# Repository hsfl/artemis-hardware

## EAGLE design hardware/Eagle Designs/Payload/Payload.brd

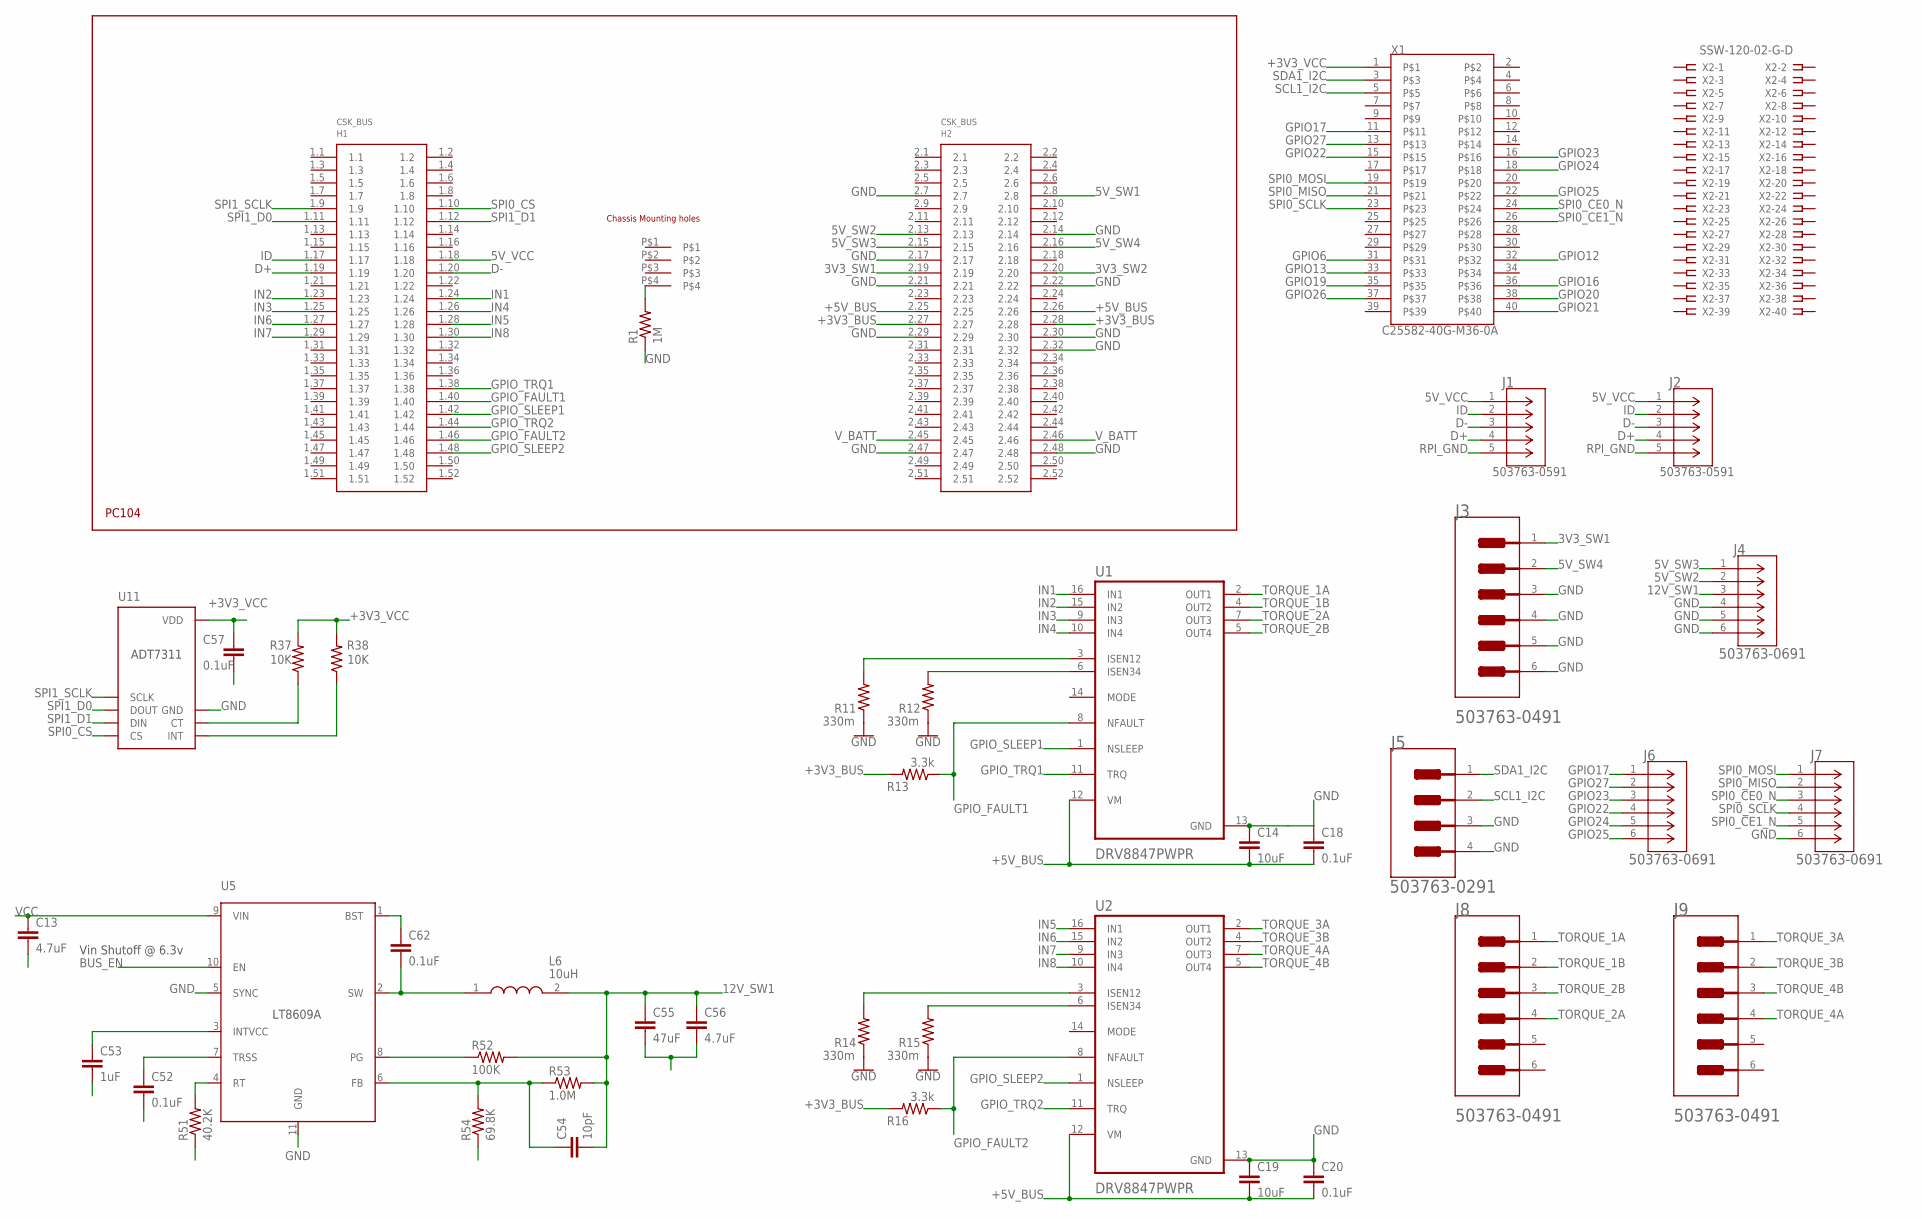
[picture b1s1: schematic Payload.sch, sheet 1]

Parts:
C13, C56: 4.7uF; 0805
C14, C19: 10uF; 0805
C18, C20, C52, C57, C62: 0.1uF; 0805
C53: 1uF; 0805
C54: 10pF; 0805
C55: 47uF; 1210
H1: PC104_WCONN
J1, J2: 503763-0591; CONN_5037630591_MOL
J3, J8, J9: MOLEX_503763-0491MOLEX_503763-0491_0_0; MOLEX_503763-0491_0
J4, J6, J7: 503763-0691; CONN_503763-0691_MOL
J5: MOLEX_503763-0291MOLEX_503763-0291_0_0; MOLEX_503763-0291_0
L6: 10uH; XFL4030472MEB
R1: 1M; 0805
R11, R12, R14, R15: 330m; 0805
R13, R16: 3.3k; 0805
R37, R38: 10K; 0805
R51: 40.2K; 0805
R52: 100K; 0805
R53: 1.0M; 0805
R54: 69.8K; 0805
U1, U2: DRV8847PWPR; SOP65P640X120-17N
U5: LT8609A; MSOP-10_MSE
U11: ADT7311; SOIC-8
X1: C25582-40G-M36-0A; ADAFRUIT_C25582-40G-M36-0A_0
X2: SSW-120-02-G-D

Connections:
3V3_SW1: H1.2.19, J3.1
3V3_SW2: H1.2.20
5V_SW1: H1.2.8
5V_SW2: H1.2.13, J4.2
5V_SW3: H1.2.15, J4.1
5V_SW4: H1.2.16, J3.2
5V_VCC: H1.1.18, J1.1, J2.1
12V_SW1: C54.2, C55.1, C56.1, J4.3, L6.2, R52.2, R53.2
+3V3_BUS: H1.2.27, H1.2.28, R13.2, R16.2
+3V3_VCC: C57.1, R37.2, R38.2, U11.8 (VDD), X1.1
+5V_BUS: C14.2, C18.2, C19.2, C20.2, H1.2.25, H1.2.26, U1.12 (VM), U2.12 (VM)
BST_3V3_BUS: C62.1, U5.1 (BST)
BUS_EN: U5.10 (EN)
D+: H1.1.19, J1.4, J2.4
D-: H1.1.20, J1.3, J2.3
FB_3V3_BUS: C54.1, R53.1, R54.2, U5.6 (FB)
GND: C14.1, C18.1, C19.1, C20.1, C52.2, C53.2, C55.2, C56.2, C57.2, H1.2.7, H1.2.14, H1.2.17, H1.2.21, H1.2.22, H1.2.29, H1.2.30, H1.2.32, H1.2.47, H1.2.48, J3.3, J3.4, J3.5 (MNT_1), J3.6 (MNT_2), J4.4, J4.5, J4.6, J5.3 (MNT_1), J5.4 (MNT_2), J7.6, R1.1, R11.1, R12.1, R14.1, R15.1, R51.1, R54.1, U1.13 (GND), U2.13 (GND), U5.5 (SYNC), U5.11 (GND), U11.7 (GND); also elsewhere on the board
GND1: C13.2
GPIO6: X1.31
GPIO12: X1.32
GPIO13: X1.33
GPIO16: X1.36
GPIO17: J6.1, X1.11
GPIO19: X1.35
GPIO20: X1.38
GPIO21: X1.40
GPIO22: J6.4, X1.15
GPIO23: J6.3, X1.16
GPIO24: J6.5, X1.18
GPIO25: J6.6, X1.22
GPIO26: X1.37
GPIO27: J6.2, X1.13
GPIO_FAULT1: H1.1.40, R13.1, U1.8 (NFAULT)
GPIO_FAULT2: H1.1.46, R16.1, U2.8 (NFAULT)
GPIO_SLEEP1: H1.1.42, U1.1 (NSLEEP)
GPIO_SLEEP2: H1.1.48, U2.1 (NSLEEP)
GPIO_TRQ1: H1.1.38, U1.11 (TRQ)
GPIO_TRQ2: H1.1.44, U2.11 (TRQ)
ID: H1.1.17, J1.2, J2.2
IN1: H1.1.24, U1.16 (IN1)
IN2: H1.1.23, U1.15 (IN2)
IN3: H1.1.25, U1.9 (IN3)
IN4: H1.1.26, U1.10 (IN4)
IN5: H1.1.28, U2.16 (IN1)
IN6: H1.1.27, U2.15 (IN2)
IN7: H1.1.29, U2.9 (IN3)
IN8: H1.1.30, U2.10 (IN4)
unnamed: H1.P$4, R1.2
unnamed: R12.2, U1.6 (ISEN34)
unnamed: R11.2, U1.3 (ISEN12)
unnamed: R15.2, U2.6 (ISEN34)
unnamed: R14.2, U2.3 (ISEN12)
PG_3V3_BUS: R52.1, U5.8 (PG)
RPI_GND: J1.5, J2.5
RT_3V3_BUS: R51.2, U5.4 (RT)
SCL1_I2C: J5.2, X1.5
SDA1_I2C: J5.1, X1.3
SPI0_CE0_N: J7.3, X1.24
SPI0_CE1_N: J7.5, X1.26
SPI0_CS: H1.1.10, U11.4 (CS)
SPI0_MISO: J7.2, X1.21
SPI0_MOSI: J7.1, X1.19
SPI0_SCLK: J7.4, X1.23
SPI1_D0: H1.1.11, U11.2 (DOUT)
SPI1_D1: H1.1.12, U11.3 (DIN)
SPI1_SCLK: H1.1.9, U11.1 (SCLK)
SW_3V3_BUS: C62.2, L6.1, U5.2 (SW)
TORQUE_1A: J8.1, U1.2 (OUT1)
TORQUE_1B: J8.2, U1.4 (OUT2)
TORQUE_2A: J8.4, U1.7 (OUT3)
TORQUE_2B: J8.3, U1.5 (OUT4)
TORQUE_3A: J9.1, U2.2 (OUT1)
TORQUE_3B: J9.2, U2.4 (OUT2)
TORQUE_4A: J9.4, U2.7 (OUT3)
TORQUE_4B: J9.3, U2.5 (OUT4)
TRSS_3V3_BUS: C52.1, U5.7 (TRSS)
U11_CT: R37.1, U11.6 (CT)
U11_INT: R38.1, U11.5 (INT)
VCC: C13.1, U5.9 (VIN); also elsewhere on the board
VCC_3V3_BUS: C53.1, U5.3 (INTVCC)
V_BATT: H1.2.45, H1.2.46; also elsewhere on the board

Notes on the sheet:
Vin Shutoff @ 6.3v

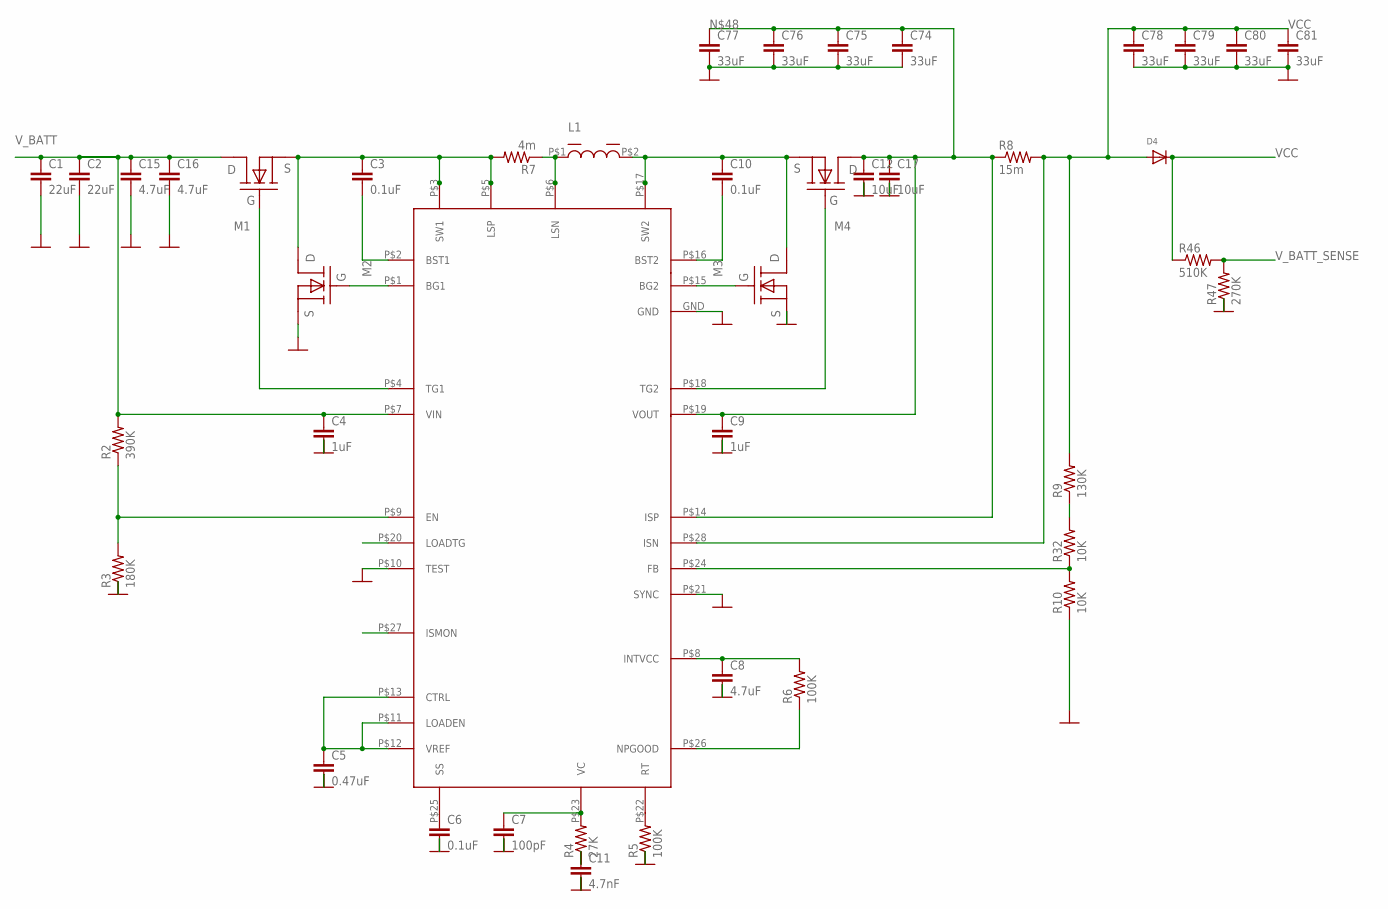
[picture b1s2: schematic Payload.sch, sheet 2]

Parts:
C1, C2: 22uF; 0805
C3, C6, C10: 0.1uF; 0805
C4, C9: 1uF; 0805
C5: 0.47uF; 0805
C7: 100pF; 0805
C8, C15, C16: 4.7uF; 0805
C11: 4.7nF; 0805
C12, C17: 10uF; 0805
C74, C75, C76, C77, C78, C79, C80, C81: 33uF; 1206
D4: DIODE_SOD-123FL; SOD-123FL
L1: 6uH; 7443551600
M1, M2: BSZ100N06LS3
M3, M4: BSZ033NE2LS5; BSZ100N06LS3
R2: 390K; 0805
R3: 180K; 0805
R4: 27K; 0805
R5, R6: 100K; 0805
R7: 4m; 0805
R8: 15m; 0805
R9: 130K; 0805
R10, R32: 10K; 0805
R46: 510K; 0805
R47: 270K; 0805
U$2: LT8309EFE

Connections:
GND: C1.2, C2.2, C4.2, C5.2, C6.2, C7.2, C8.2, C9.2, C11.2, C12.2, C15.2, C16.2, C17.2, C74.2, C75.2, C76.2, C77.2, C78.2, C79.2, C80.2, C81.2, M2.P$2 (S), M2.P$3 (S), M2.P$4 (S), M3.P$2 (S), M3.P$3 (S), M3.P$4 (S), R3.1, R5.1, R10.1, R47.1, U$2.GND, U$2.P$10 (TEST), U$2.P$21 (SYNC); also elsewhere on the board
unnamed: C3.1, M1.P$2 (S), M1.P$3 (S), M1.P$4 (S), M2.P$5 (D), M2.P$6 (D), M2.P$7 (D), M2.P$8 (D), M2.P$9 (D), R7.2, U$2.P$3 (SW1), U$2.P$5 (LSP)
unnamed: C3.2, U$2.P$2 (BST1)
unnamed: C6.1, U$2.P$25 (SS)
unnamed: R5.2, U$2.P$22 (RT)
unnamed: C10.1, L1.P$2, M3.P$5 (D), M3.P$6 (D), M3.P$7 (D), M3.P$8 (D), M3.P$9 (D), M4.P$2 (S), M4.P$3 (S), M4.P$4 (S), U$2.P$17 (SW2)
unnamed: R9.1, R32.2
unnamed: M2.P$1 (G), U$2.P$1 (BG1)
unnamed: M1.P$1 (G), U$2.P$4 (TG1)
unnamed: M3.P$1 (G), U$2.P$15 (BG2)
unnamed: R2.1, R3.2, U$2.P$9 (EN)
unnamed: C5.1, U$2.P$11 (LOADEN), U$2.P$12 (VREF), U$2.P$13 (CTRL)
unnamed: C7.1, R4.2, U$2.P$23 (VC)
unnamed: R6.1, U$2.P$26 (NPGOOD)
unnamed: C8.1, R6.2, U$2.P$8 (INTVCC)
unnamed: L1.P$1, R7.1, U$2.P$6 (LSN)
unnamed: C10.2, U$2.P$16 (BST2)
unnamed: C9.1, C12.1, C17.1, C74.1, C75.1, C76.1, C77.1, M4.P$5 (D), M4.P$6 (D), M4.P$7 (D), M4.P$8 (D), M4.P$9 (D), R8.1, U$2.P$14 (ISP), U$2.P$19 (VOUT)
unnamed: M4.P$1 (G), U$2.P$18 (TG2)
unnamed: R10.2, R32.1, U$2.P$24 (FB)
unnamed: C11.1, R4.1
VCC: C78.1, C79.1, C80.1, C81.1, D4.A, D4.C, R8.2, R9.2, R46.1, U$2.P$28 (ISN); also elsewhere on the board
V_BATT: C1.1, C2.1, C4.1, C15.1, C16.1, M1.P$5 (D), M1.P$6 (D), M1.P$7 (D), M1.P$8 (D), M1.P$9 (D), R2.2, U$2.P$7 (VIN); also elsewhere on the board
V_BATT_SENSE: R46.2, R47.2

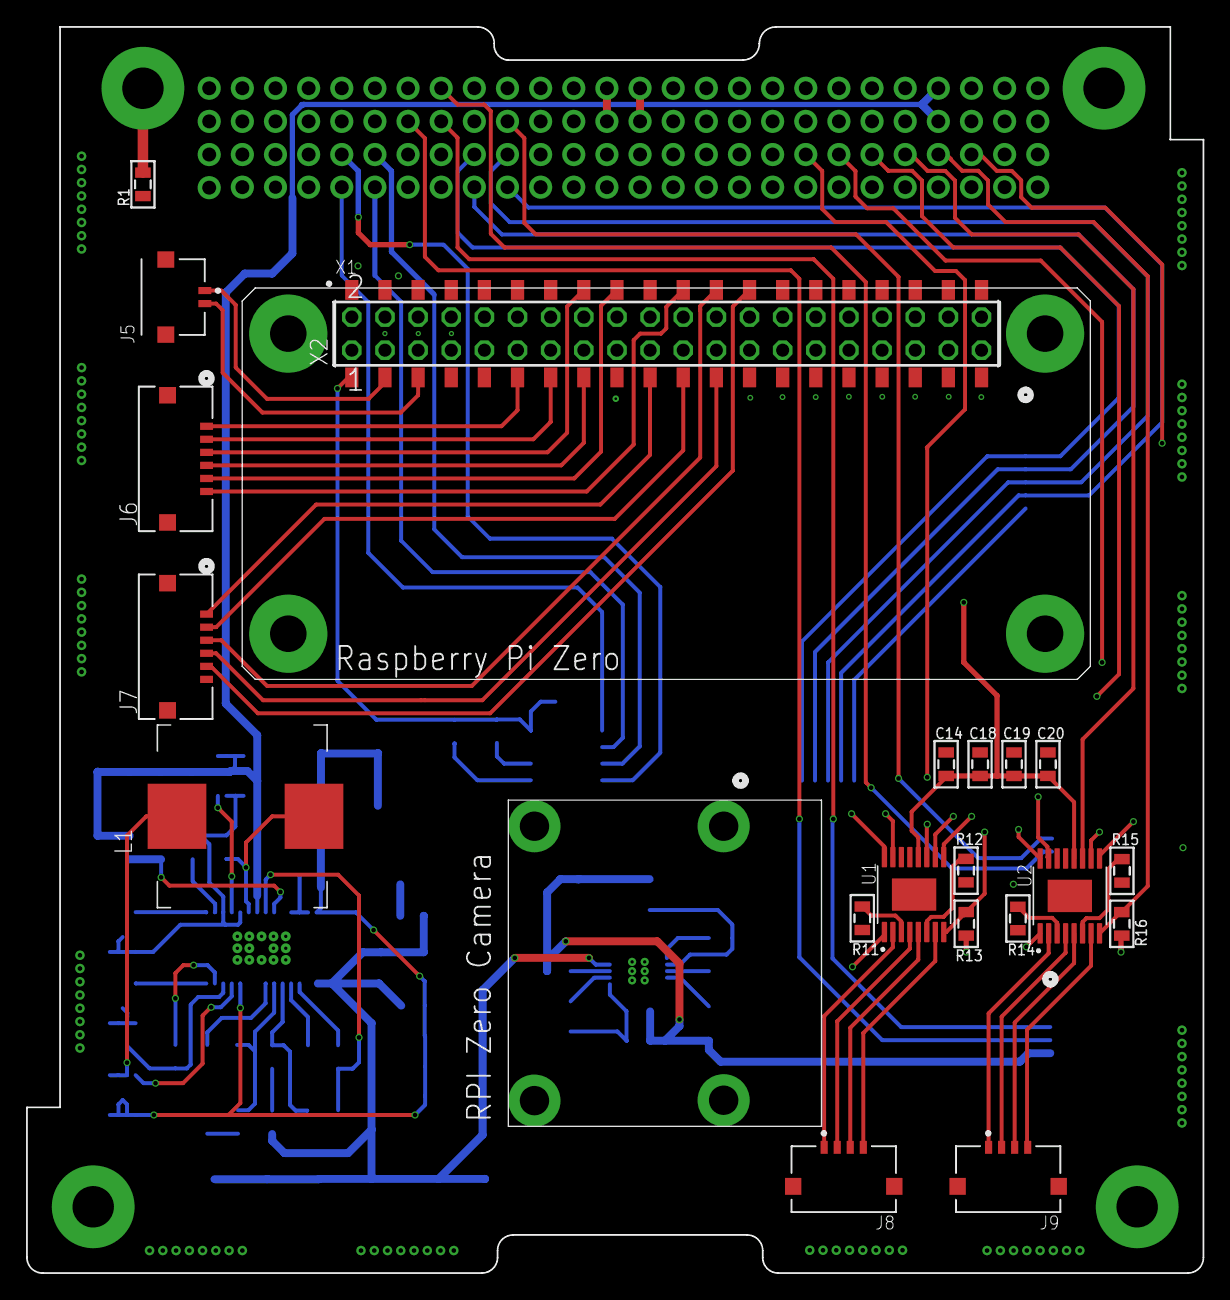
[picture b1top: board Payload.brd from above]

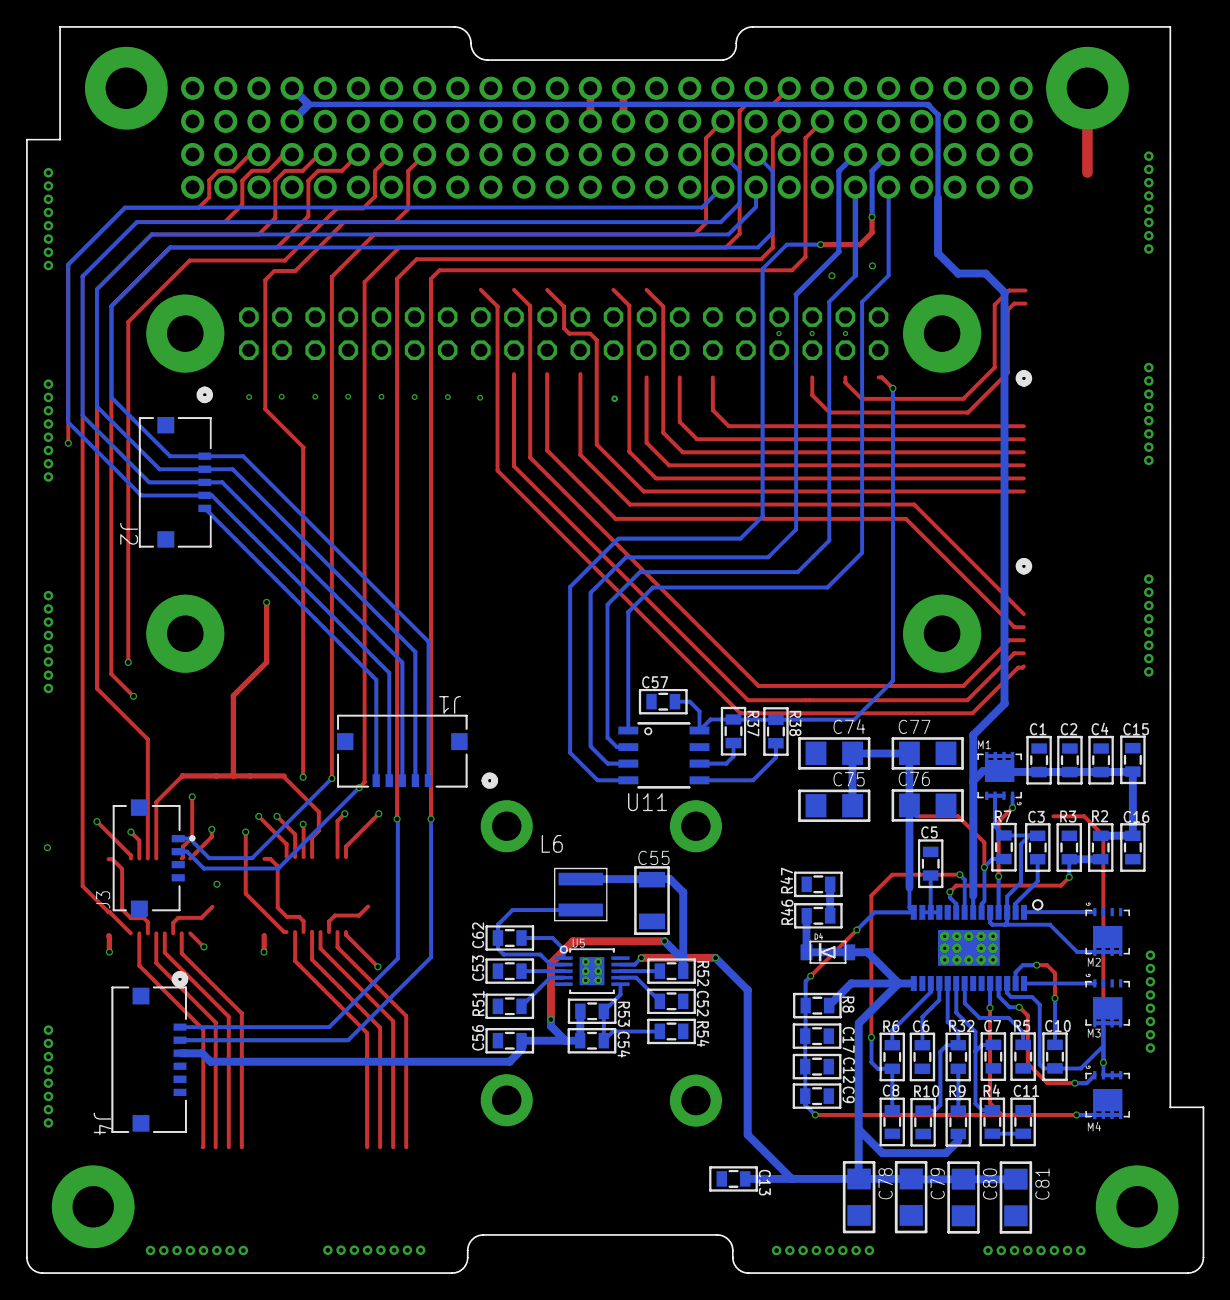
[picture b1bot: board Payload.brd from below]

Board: 4 copper layers, 90.2 x 95.5 mm, 84 parts (62 on the bottom side), 90 nets.

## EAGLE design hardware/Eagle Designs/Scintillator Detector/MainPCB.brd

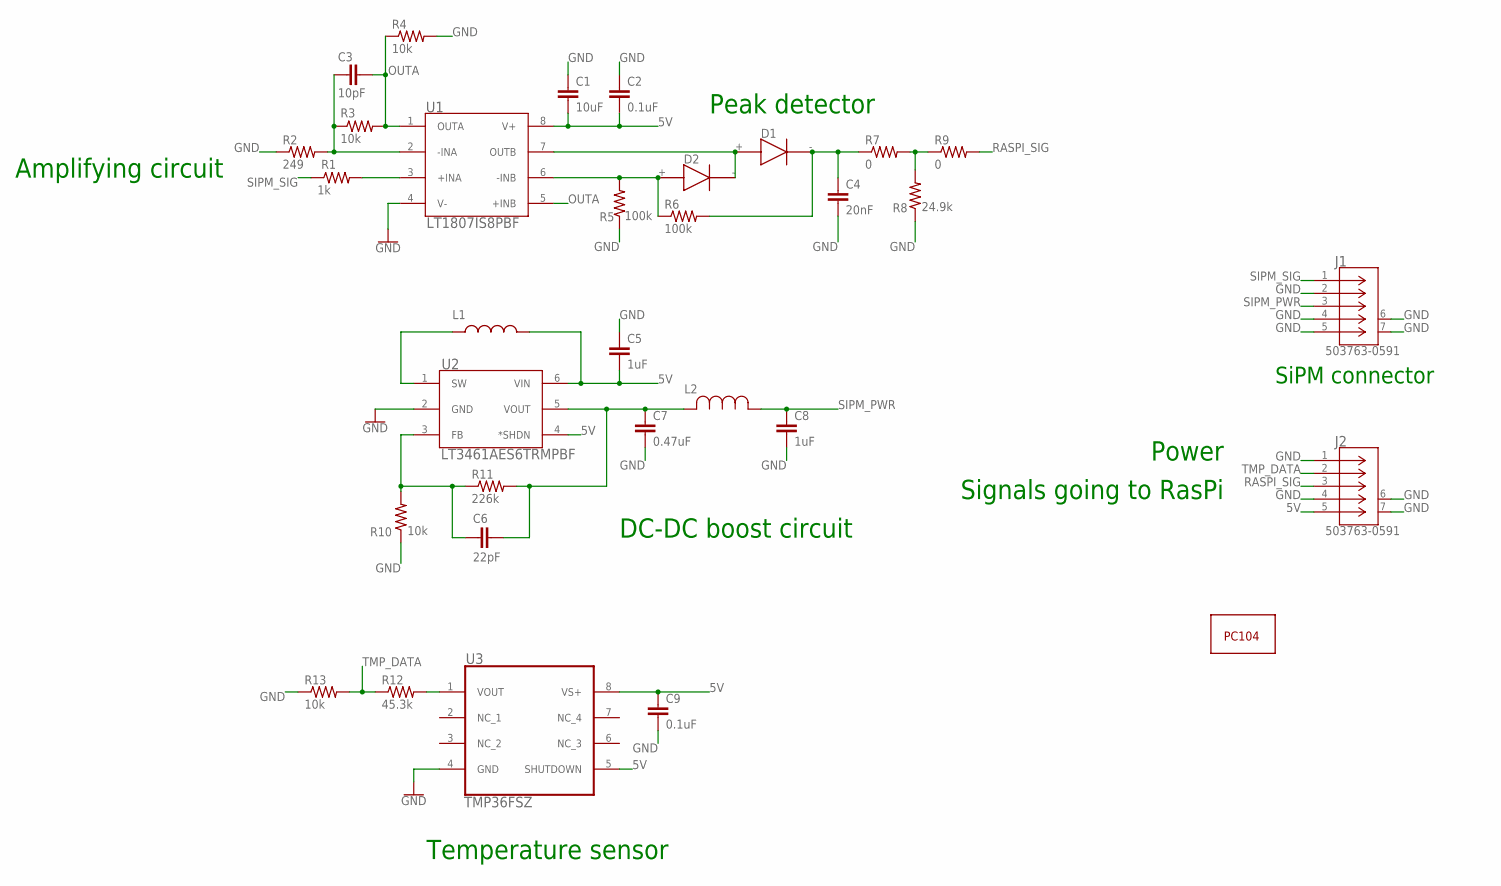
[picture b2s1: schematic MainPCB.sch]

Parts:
C1: 10uF; 0805
C2, C9: 0.1uF; 0805
C3: 10pF; 0805
C4: 20nF; 0805
C5, C8: 1uF; 0805
C6: 22pF; 0805
C7: 0.47uF; 0805
D1, D2: RBR1VWM40ATR
J1, J2: 503763-0591; CONN_5037630591_MOL
L1: 47uH; IND_LQH32CN470K53L
L2: BK2125LM252-T; BK2125HS_TAY
R1: 1k; 0805
R2: 249; 0805
R3, R4, R10, R13: 10k; 0805
R5, R6: 100k; 0805
R7, R9: 0; 0805
R8: 24.9k; 0805
R11: 226k; 0805
R12: 45.3k; 0805
U1: LT1807IS8PBF; MSOP-8_MS_LIT
U2: LT3461AES6TRMPBF; TSOT-23_S6
U3: TMP36FSZ; SOIC127P600X175-8N
U$1: PC104_WCONN_DETECTOR

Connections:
5V: C1.2, C2.2, C5.2, C9.1, J2.5, L1.2, U1.8 (V+), U2.4 (*SHDN), U2.6 (VIN), U3.5 (SHUTDOWN), U3.8 (VS+)
GND: C1.1, C2.1, C4.2, C5.1, C7.2, C8.2, C9.2, J1.2, J1.4, J1.5, J1.6, J1.7, J2.1, J2.4, J2.6, J2.7, R2.1, R4.2, R5.1, R8.1, R10.1, R13.1, U1.4 (V-), U2.2 (GND), U3.4 (GND)
unnamed: R1.2, U1.3 (+INA)
unnamed: C3.1, R2.2, R3.1, U1.2 (-INA)
unnamed: D2.+, R5.2, R6.1, U1.6 (-INB)
unnamed: C4.1, D1.-, R6.2, R7.1
unnamed: D1.+, D2.-, U1.7 (OUTB)
unnamed: R7.2, R8.2, R9.1
unnamed: L1.1, U2.1 (SW)
unnamed: C6.1, R10.2, R11.1, U2.3 (FB)
unnamed: C6.2, C7.1, L2.2, R11.2, U2.5 (VOUT)
unnamed: R12.2, U3.1 (VOUT)
OUTA: C3.2, R3.2, R4.1, U1.1 (OUTA), U1.5 (+INB)
RASPI_SIG: J2.3, R9.2
SIPM_PWR: C8.1, J1.3, L2.1
SIPM_SIG: J1.1, R1.1
TMP_DATA: J2.2, R12.1, R13.2

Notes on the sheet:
Amplifying circuit
Peak detector
DC-DC boost circuit
Temperature sensor
SiPM connector
Power
Signals going to RasPi

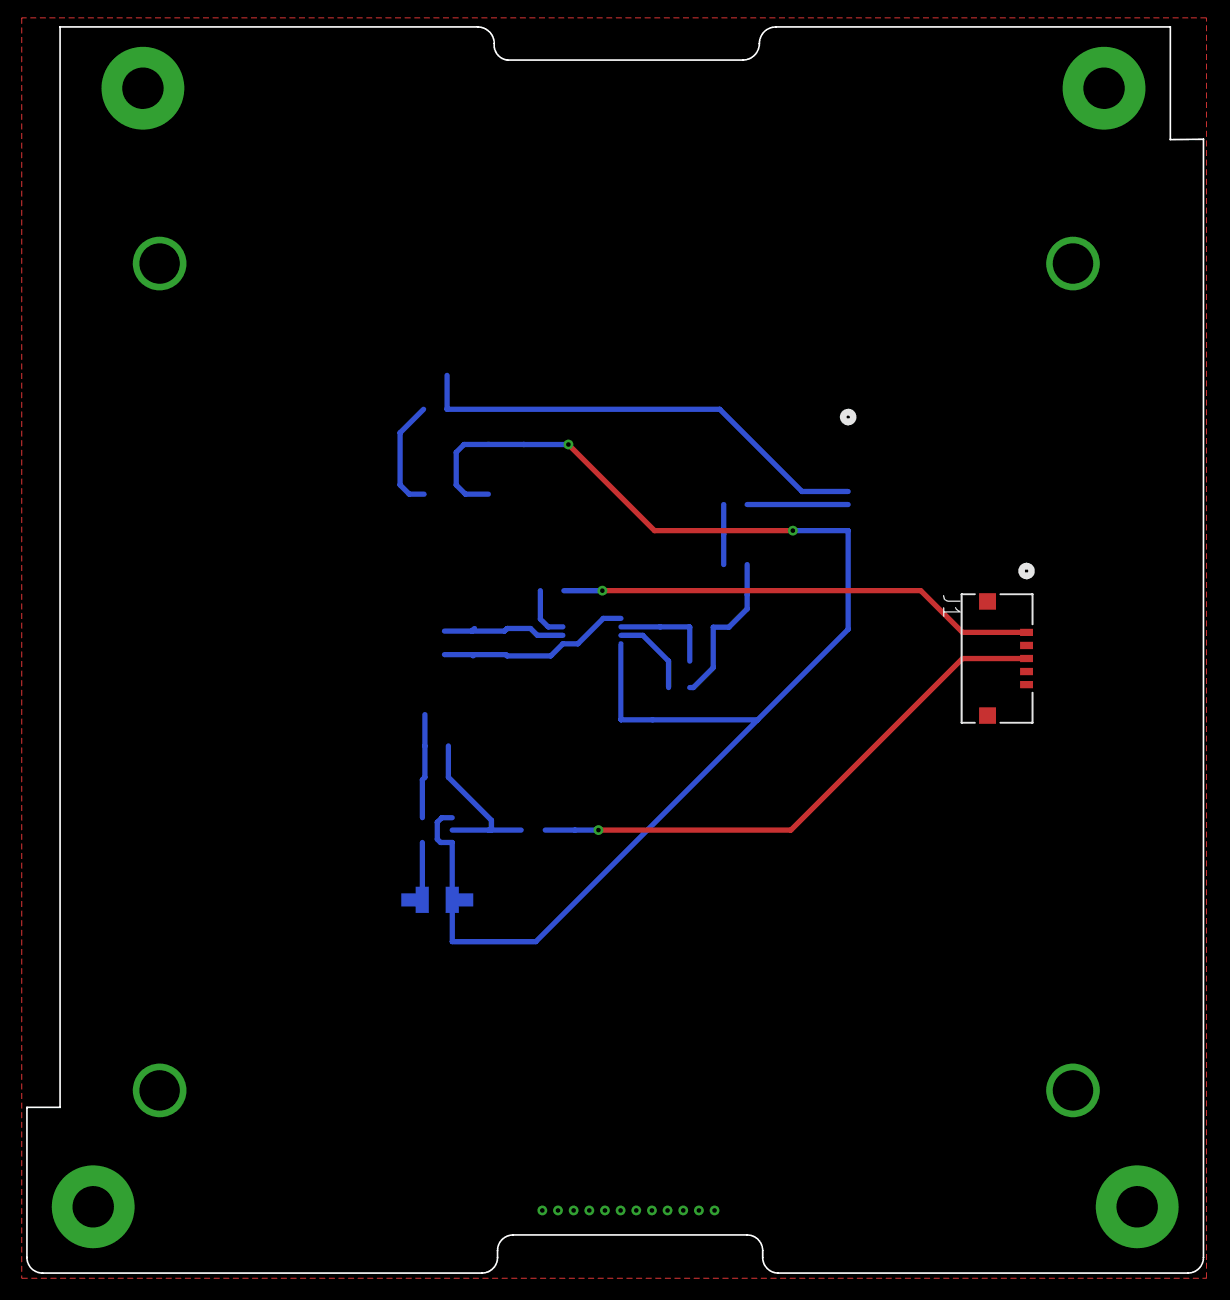
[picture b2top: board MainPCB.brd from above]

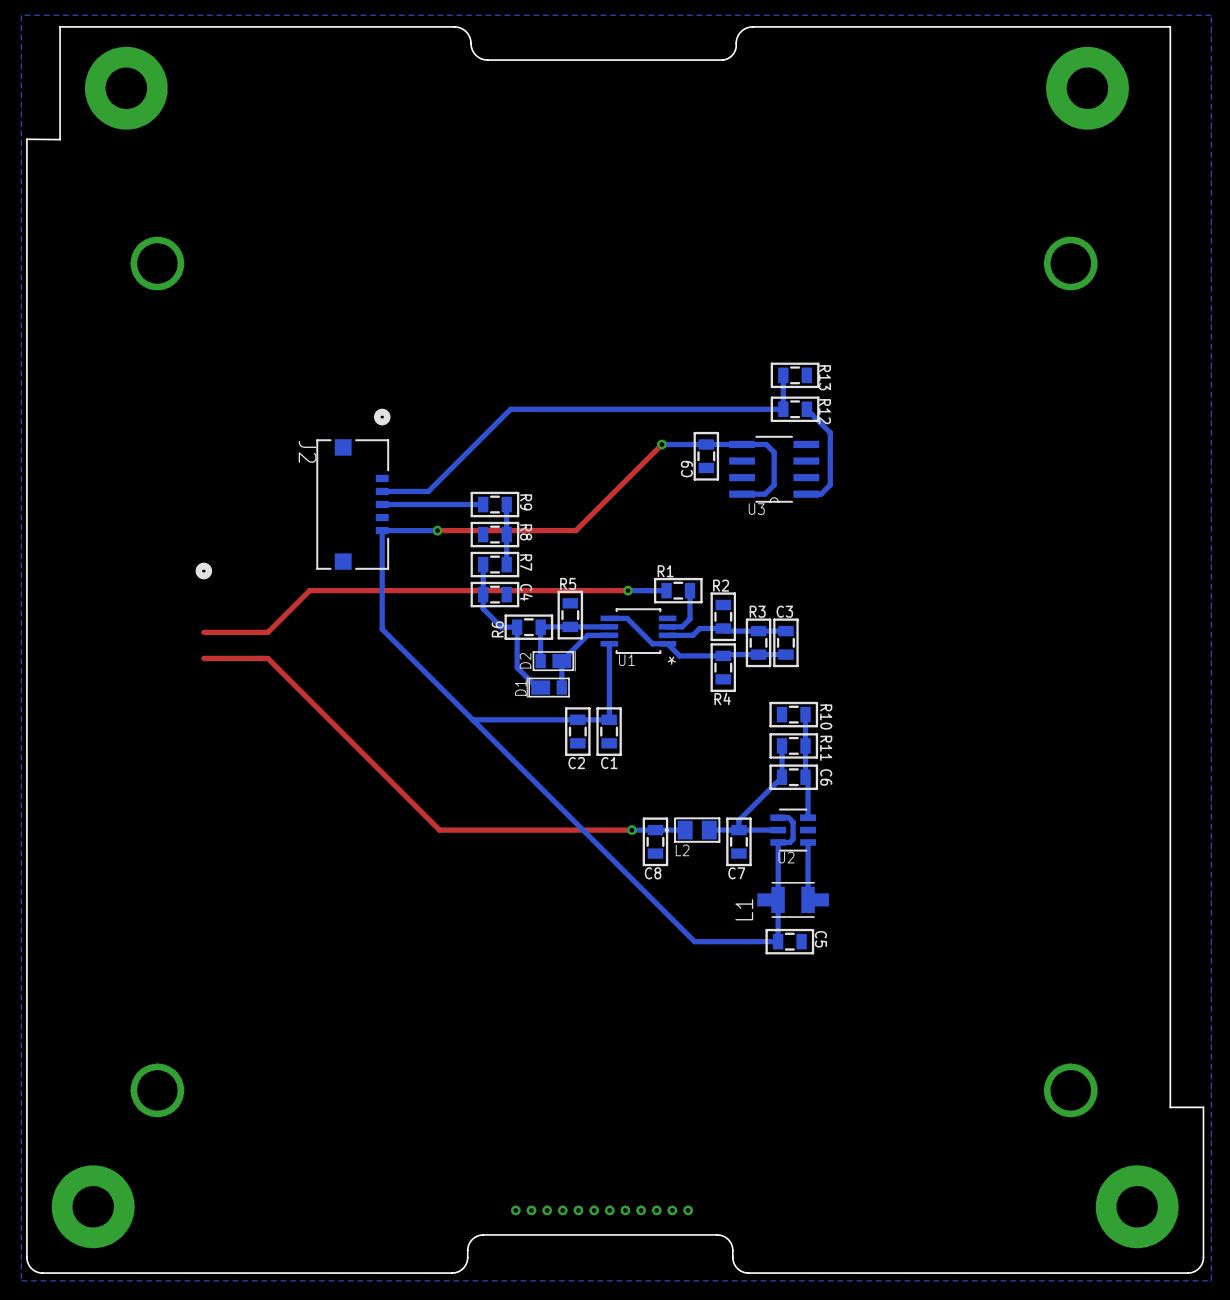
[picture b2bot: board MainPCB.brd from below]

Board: 2 copper layers, 90.2 x 95.5 mm, 32 parts (30 on the bottom side), 17 nets.

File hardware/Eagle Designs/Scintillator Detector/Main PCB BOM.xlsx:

Part | Value | Device
C1 | 10uF | CAP0805
C2, C9 | 0.1uF | CAP0805
C3 | 10pF | CAP0805
C4 | 20nF | CAP0805
C5, C8 | 1uF | CAP0805
C6 | 22pF | CAP0805
C7 | 0.47uF | CAP0805
D1, D2 | RBR1VWM40ATR | RBR1VWM40ATR
J1, J2 | 503763-0591 | 503763-0591
L1 | 47uH | LQH32CN470K53L
L2 | BK2125LM252-T | BK2125LM252-T
R1 | 1k | RESISTOR0805-RES
R2 | 249 | RESISTOR0805-RES
R3, R4, R10, R13 | 10k | RESISTOR0805-RES
R5, R6 | 100k | RESISTOR0805-RES
R7, R9 | 0 | RESISTOR0805-RES
R8 | 24.9k | RESISTOR0805-RES
R11 | 226k | RESISTOR0805-RES
R12 | 45.3k | RESISTOR0805-RES
U1 | LT1807IS8PBF | LT1807IS8PBF
U2 | LT3461AES6TRMPBF | LT3461AES6TRMPBF
U3 | TMP36GSZ | TMP36GSZ

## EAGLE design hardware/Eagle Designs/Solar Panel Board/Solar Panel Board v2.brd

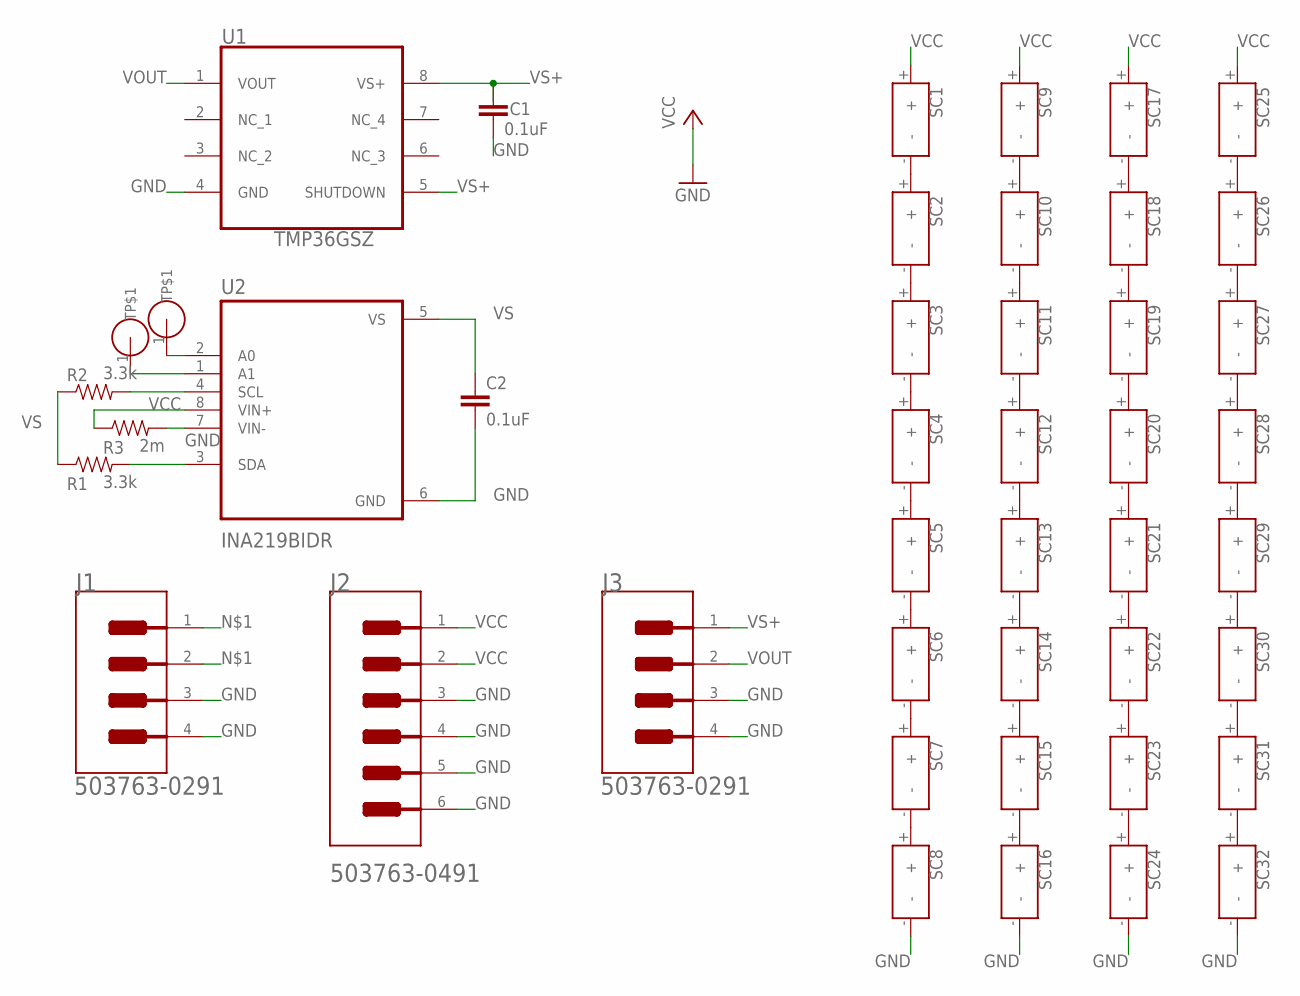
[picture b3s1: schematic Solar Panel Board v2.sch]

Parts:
C1, C2: 0.1uF; 0805
J1, J3: MOLEX_503763-0291MOLEX_503763-0291_0_0; MOLEX_503763-0291_0
J2: MOLEX_503763-0491MOLEX_503763-0491_0_0; MOLEX_503763-0491_0
R1, R2: 3.3k; 0805
R3: 2m; 0805
SC1, SC2, SC3, SC4, SC5, SC6, SC7, SC8, SC9, SC10, SC11, SC12, SC13, SC14, SC15, SC16, SC17, SC18, SC19, SC20, SC21, SC22, SC23, SC24, SC25, SC26, SC27, SC28, SC29, SC30, SC31, SC32: KXOB25-05X3F
U1: TMP36GSZ; SOIC127P600X175-8N
U2: INA219BIDR; SOIC127P599X175-8N
U$1, U$2: TEST_POINT

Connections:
GND: C1.2, C2.2, J1.3 (MNT_1), J1.4 (MNT_2), J2.3, J2.4, J2.5 (MNT_1), J2.6 (MNT_2), J3.3 (MNT_1), J3.4 (MNT_2), R3.2, SC8.-, SC16.-, SC24.-, SC32.-, U1.4 (GND), U2.6 (GND), U2.7 (VIN-)
unnamed: J1.1, J1.2
unnamed: SC1.-, SC2.+
unnamed: SC2.-, SC3.+
unnamed: SC3.-, SC4.+
unnamed: SC4.-, SC5.+
unnamed: SC5.-, SC6.+
unnamed: SC6.-, SC7.+
unnamed: SC7.-, SC8.+
unnamed: SC9.-, SC10.+
unnamed: SC10.-, SC11.+
unnamed: SC11.-, SC12.+
unnamed: SC12.-, SC13.+
unnamed: SC13.-, SC14.+
unnamed: SC14.-, SC15.+
unnamed: SC15.-, SC16.+
unnamed: SC17.-, SC18.+
unnamed: SC18.-, SC19.+
unnamed: SC19.-, SC20.+
unnamed: SC20.-, SC21.+
unnamed: SC21.-, SC22.+
unnamed: SC22.-, SC23.+
unnamed: SC23.-, SC24.+
unnamed: SC25.-, SC26.+
unnamed: SC26.-, SC27.+
unnamed: SC27.-, SC28.+
unnamed: SC28.-, SC29.+
unnamed: SC29.-, SC30.+
unnamed: SC30.-, SC31.+
unnamed: SC31.-, SC32.+
unnamed: U2.2 (A0), U$1.1
unnamed: U2.1 (A1), U$2.1
unnamed: R2.2, U2.4 (SCL)
unnamed: R1.2, U2.3 (SDA)
VCC: J2.1, J2.2, R3.1, SC1.+, SC9.+, SC17.+, SC25.+, U2.8 (VIN+)
VOUT: J3.2, U1.1 (VOUT)
VS: C2.1, R1.1, R2.1, U2.5 (VS)
VS+: C1.1, J3.1, U1.5 (SHUTDOWN), U1.8 (VS+)

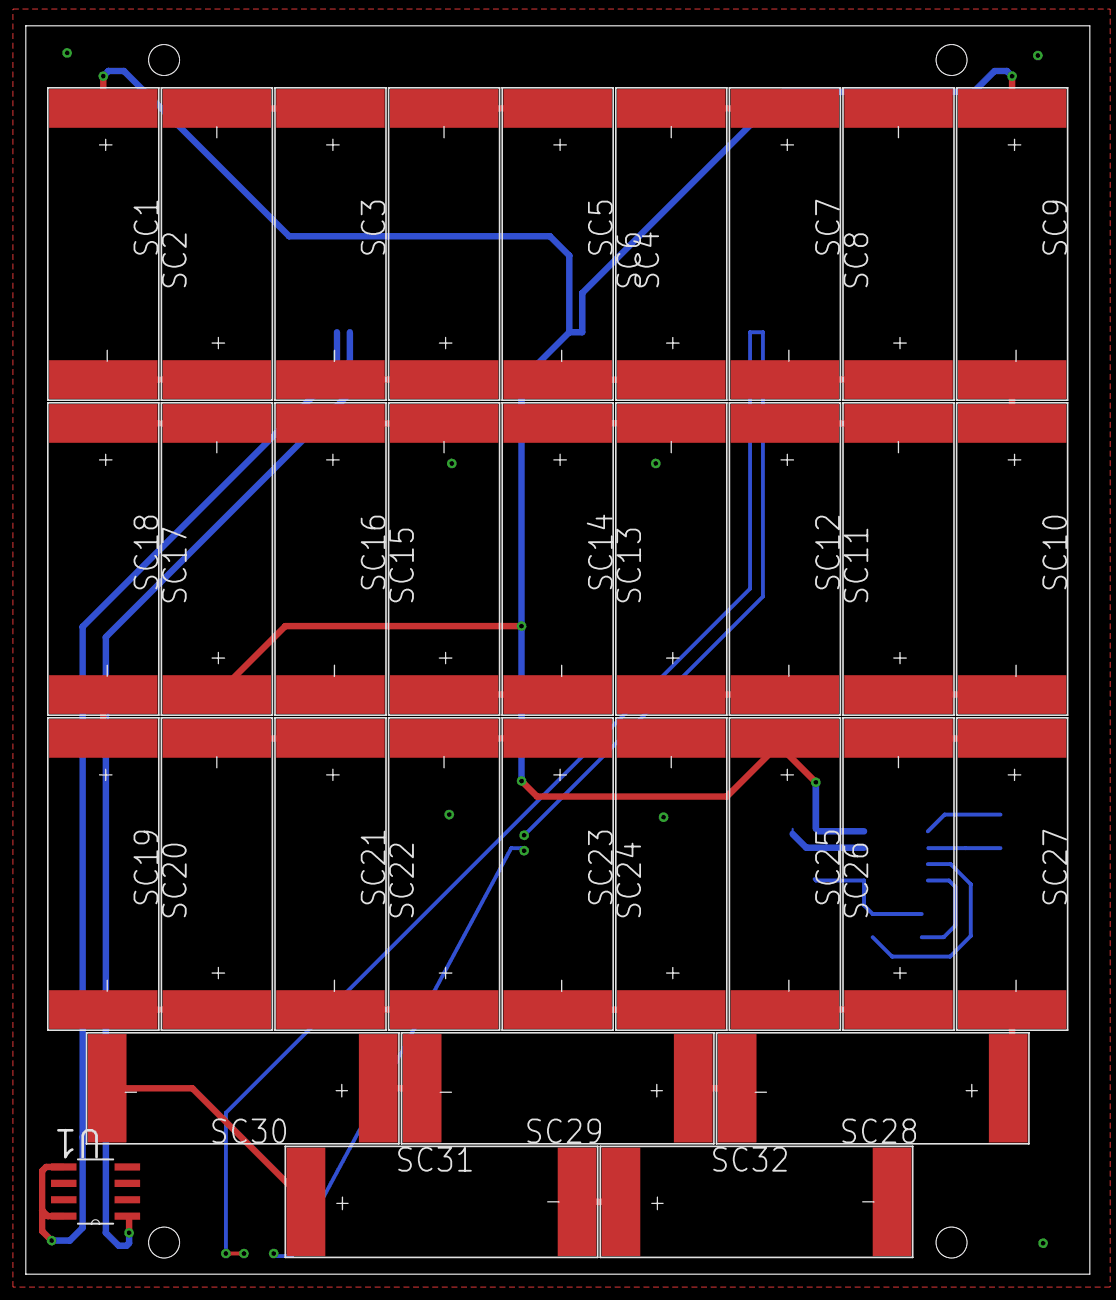
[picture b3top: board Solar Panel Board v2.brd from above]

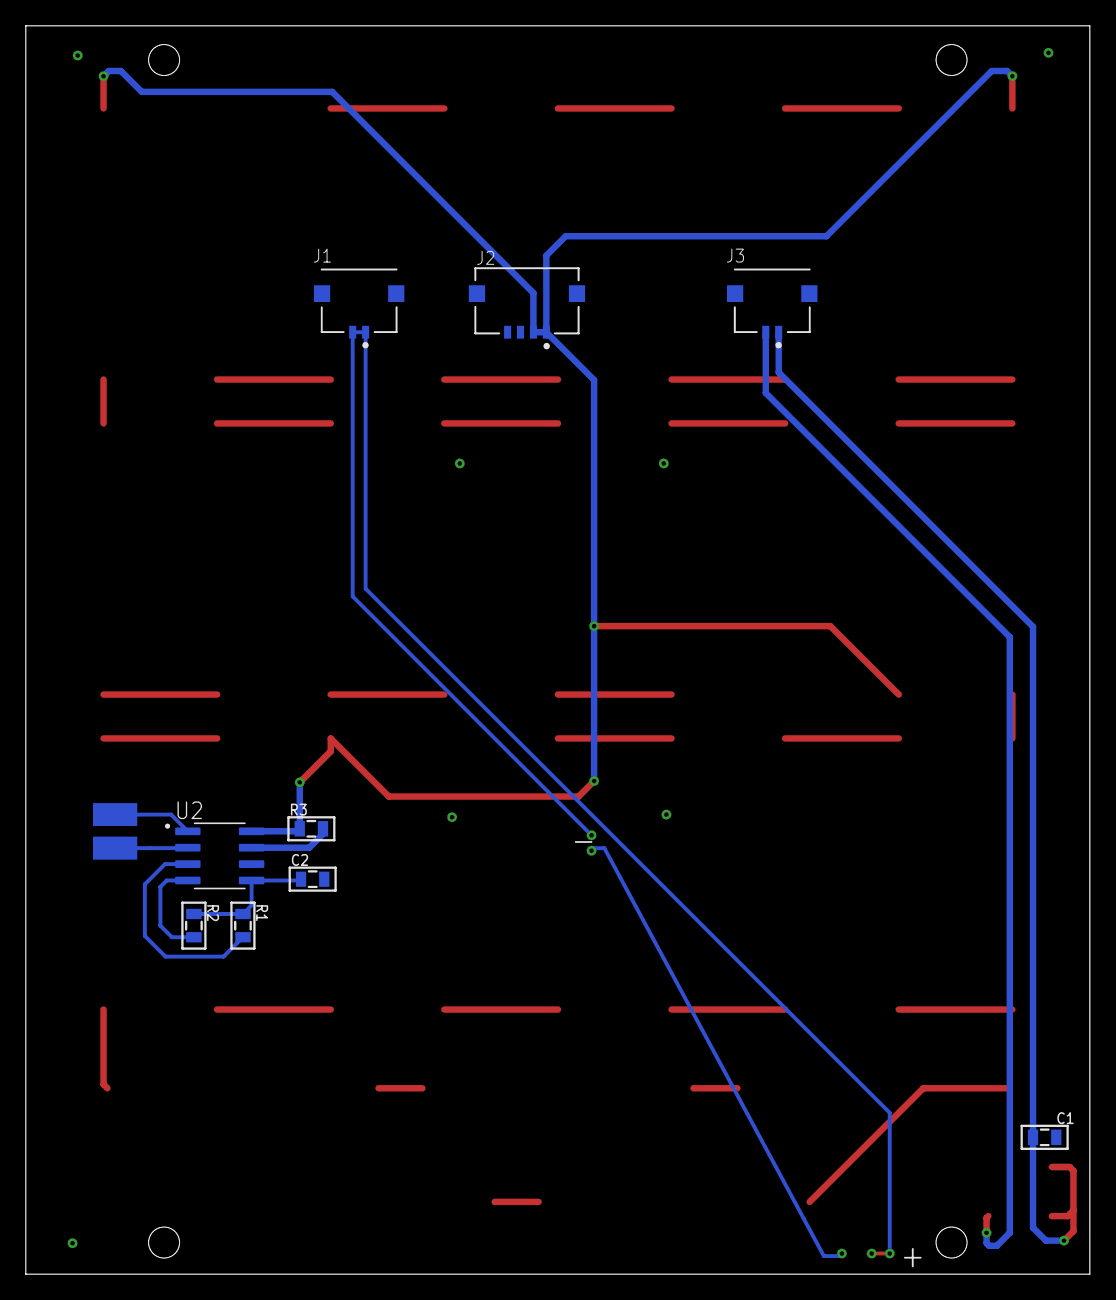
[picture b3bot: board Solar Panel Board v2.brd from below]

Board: 4 copper layers, 82.4 x 96.7 mm, 44 parts (11 on the bottom side), 38 nets.

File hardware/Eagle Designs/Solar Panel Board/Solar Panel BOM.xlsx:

Part | Value | Device | Package | Description
C1, C2 | 0.1uF | CAP0805 | *0805 | Capacitor
J1, J3 | 503763-0291 | MOLEX_503763-0291MOLEX_503763-0291_0_0 | MOLEX_503763-0291_0 | 2 Positions Header Connector 0.039 (1.00mm) Surface Mount, Right Angle Gold"
J2 | 503763-0491 | MOLEX_503763-0491MOLEX_503763-0491_0_0 | MOLEX_503763-0491_0 | Wire-To-Board Connector, Pico-Lock 503763 Series, Surface Mount, Header, 4 Cont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
SC1 - SC32 | KXOB25-05X3F | KXOB25-05X3F | KXOB25-05X3F | MONOCRYS SOLAR CELL 30.7MW 2.07V
U1 | TMP36GSZ | TMP36GSZ | SOIC127P600X175-8N | Temperature Sensor Analog, Local -40°C ~ 125°C 10mV/°C 8-SOIC
U2 | INA219BIDR | INA219BIDR 296-27899-1-ND | INA219BIDR | IC MONITOR PWR/CURR BIDIR 8-SOIC
R1, R2 | 3.3 kΩ | RES0805 | *0805 | Resistor
R3 | 2 mΩ | RES0805 | *0805 | Resistor

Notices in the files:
parts and their libraries:
COPYRIGHT: Copyright (C) 2018 Accelerated Designs. All rights reserved
SparkFun-PowerSymbols: Licensing: Creative Commons ShareAlike 4.0 International - https://creativecommons.org/licenses/by-sa/4.0
COPYRIGHT: Copyright (C) 2021 Ultra Librarian. All rights reserved.
